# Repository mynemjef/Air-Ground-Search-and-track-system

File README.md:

# Дипломна Работа

Система за търсене и проследяване на цели във въздушно пространство. Позволява намиране и проследяване на летящи и нисколетящи цели, като филтрира нежелани обекти. Системата позволява точно проследяване на бързи и бавни цели чрез усъвършенствани алгоритми.

## Използвани технологии

* LiDAR - технология за активно дистанционно засичане, която използва лазерни лъчи за измерване на разстояния в околната среда. 
* ESP32 - микроконтролер с вграден Wi-Fi и Bluetooth, предоставящ гъвкава платформа за разработка на интернет на нещата (IoT) приложения.
* FreeCAD - отворен софтуер за CAD, който позволява проектиране и моделиране на различни обекти.
* KiCAD - софтуер за проектиране на електронни схеми и печатни платки, предоставящ интегрирани инструменти за създаване на комплексни електронни устройства.

## Информация за автора на проекта

* Станислав Иванов - създател - https://github.com/mynemjef

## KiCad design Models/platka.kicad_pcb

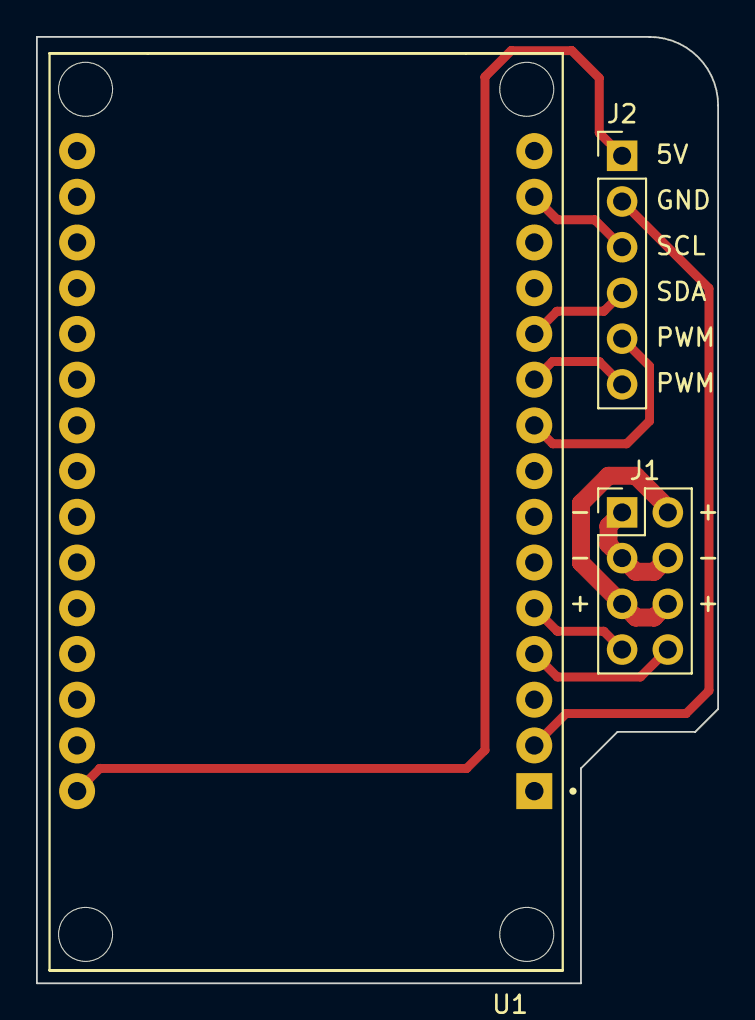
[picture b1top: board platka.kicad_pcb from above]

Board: 2 copper layers, 37.8 x 52.6 mm, 3 parts (0 on the bottom side), 10 nets.

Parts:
J1: BATTERY_AND_SERVOS_HEADER; PinHeader_2x04_P2.54mm_Vertical
J2: LIDAR_LITE_V4_HEADER; PinHeader_1x06_P2.54mm_Vertical
U1: ESP32-DEVKIT-V1; MODULE_ESP32_DEVKIT_V1

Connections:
unnamed: J1.1, J1.3, J1.4
unnamed: J1.2, J1.5, J1.6
unnamed: J1.7, U1.5 (D4)
unnamed: J1.8, U1.4 (D2)
unnamed: J2.1, U1.30 (VIN)
unnamed: J2.2, U1.2 (GND)
unnamed: J2.3, U1.14 (D22)
unnamed: J2.4, U1.11 (D21)
unnamed: J2.5, U1.9 (D18)
unnamed: J2.6, U1.10 (D19)

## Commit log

2024-05-21 Move platka.kicad_pro to Models/platka.kicad_pro
2024-05-21 Move platka.kicad_sch to Models/platka.kicad_sch
2024-05-21 Move platka.kicad_pcb to Models/platka.kicad_pcb
2024-05-21 Move display.py to Code/display.py
2024-05-21 Move main_code.ino to Code/main_code.ino
